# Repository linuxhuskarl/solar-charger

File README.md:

# solar-charger
## Projekt inżynierski 2019/2020

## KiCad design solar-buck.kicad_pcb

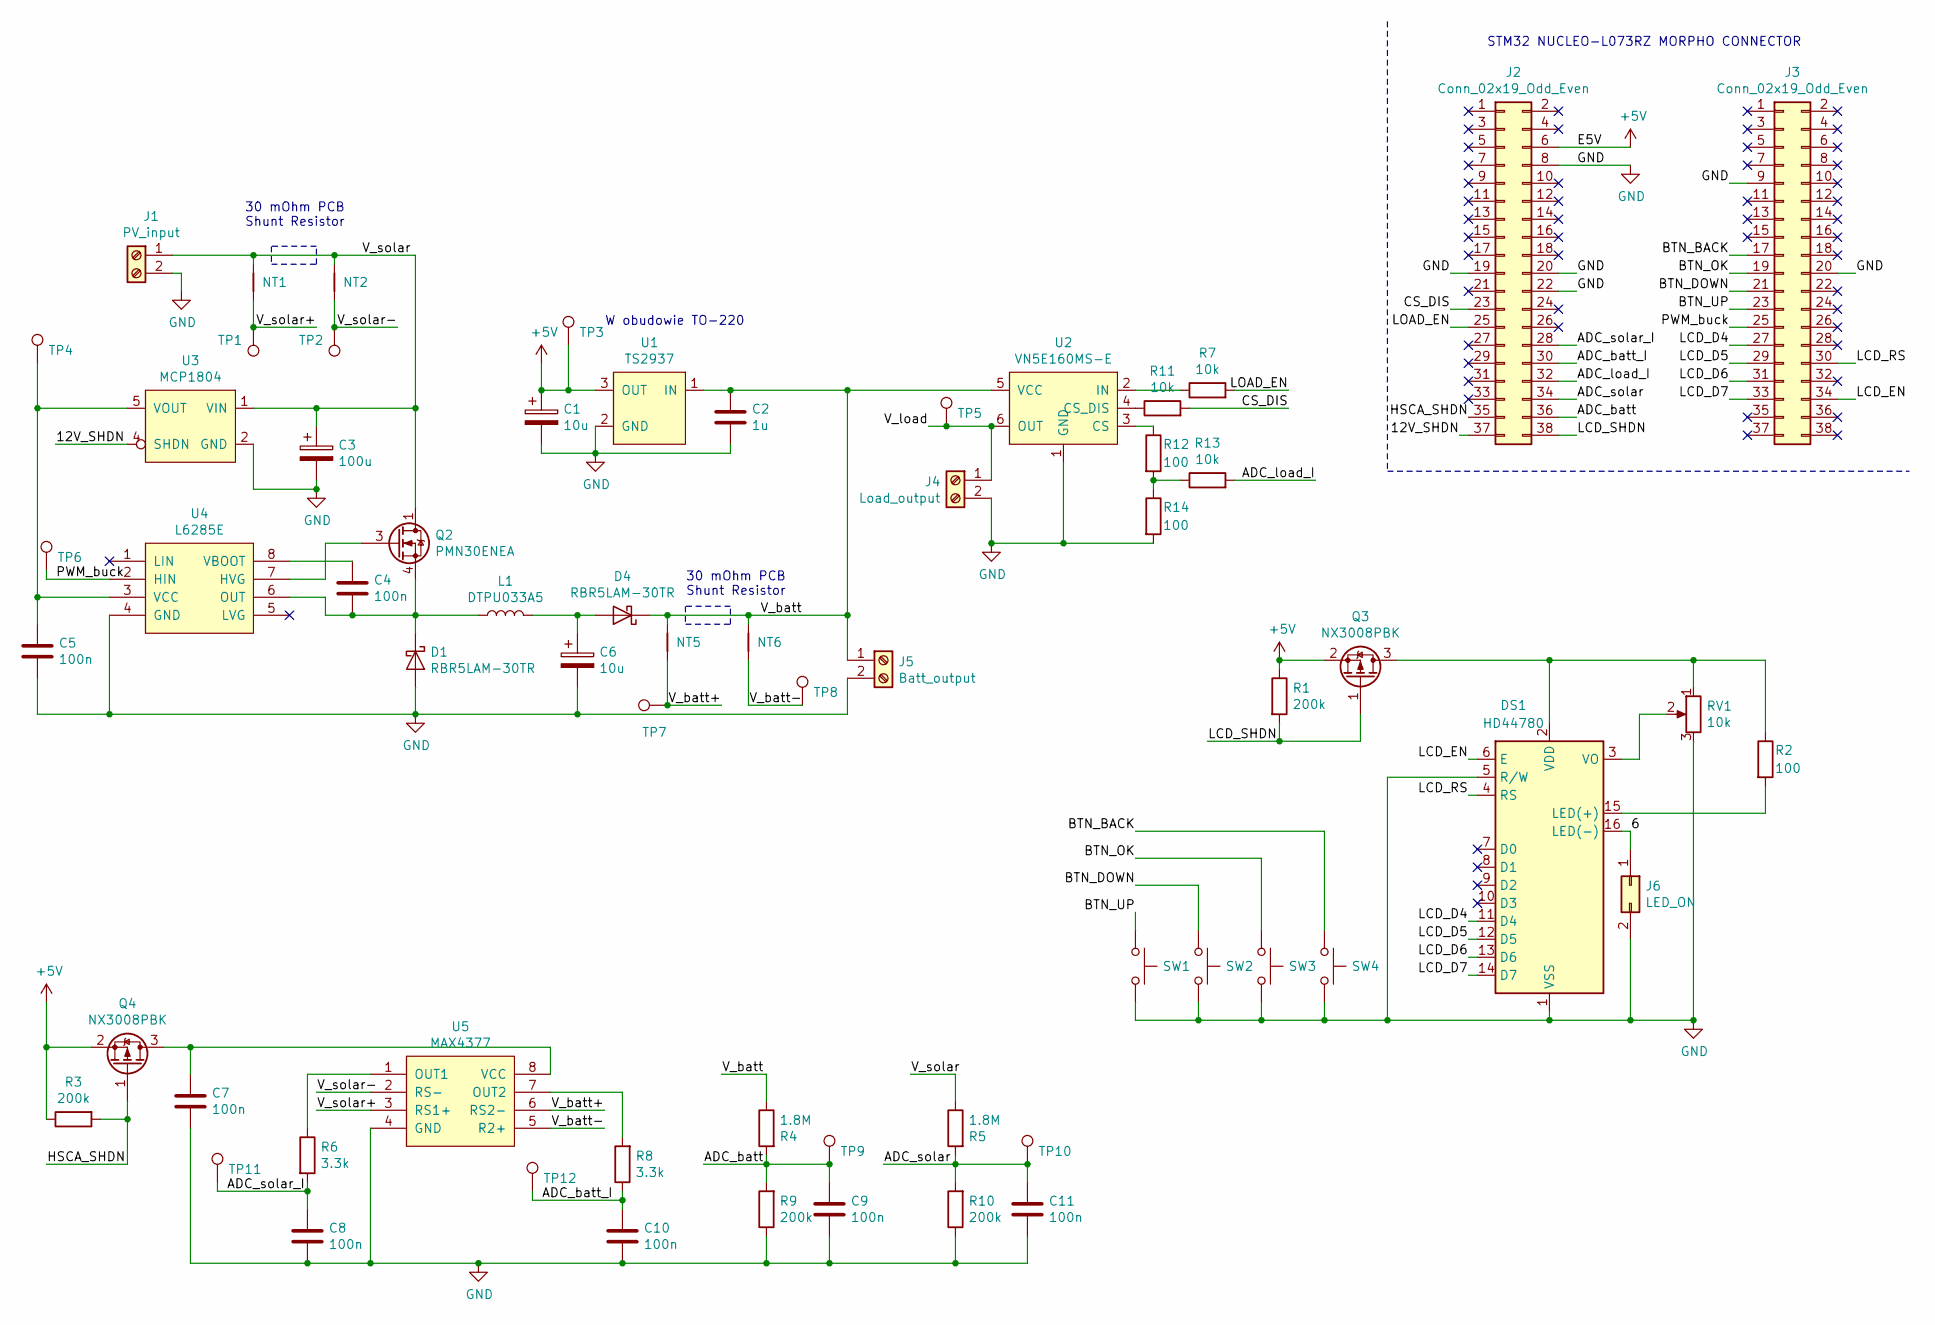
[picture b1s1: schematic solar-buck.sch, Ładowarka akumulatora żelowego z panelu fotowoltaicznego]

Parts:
C1, C6: 10u; CP_Elec_4x5.4
C2: 1u; C_0603_1608Metric_Pad1.05x0.95mm_HandSolder
C3: 100u; CP_Elec_6.3x7.7
C4, C5, C7, C8, C9, C10, C11: 100n; C_0603_1608Metric_Pad1.05x0.95mm_HandSolder
D1, D4: RBR5LAM-30TR; D_0805_2012Metric_Pad1.15x1.40mm_HandSolder
DS1: HD44780; PinSocket_1x16_P2.54mm_Vertical
J1: PV_input; TerminalBlock_bornier-2_P5.08mm
J2, J3: Conn_02x19_Odd_Even; PinSocket_2x19_P2.54mm_Vertical
J4: Load_output; TerminalBlock_bornier-2_P5.08mm
J5: Batt_output; TerminalBlock_bornier-2_P5.08mm
J6: LED_ON; PinHeader_2x01_P2.54mm_Vertical
L1: DTPU033A5
NT1, NT2, NT5, NT6: Net-Tie_2; NetTie-2_SMD_Pad8mil
Q2: PMN30ENEA; TSOP-6_1.65x3.05mm_P0.95mm
Q3, Q4: NX3008PBK; SOT-23_Handsoldering
R1, R3, R9, R10: 200k; R_0603_1608Metric_Pad1.05x0.95mm_HandSolder
R2, R12, R14: 100; R_0603_1608Metric_Pad1.05x0.95mm_HandSolder
R4, R5: 1.8M; R_0603_1608Metric_Pad1.05x0.95mm_HandSolder
R6, R8: 3.3k; R_0603_1608Metric_Pad1.05x0.95mm_HandSolder
R7, R11, R13: 10k; R_0603_1608Metric_Pad1.05x0.95mm_HandSolder
RV1: 10k; Potentiometer_Bourns_TC33X_Vertical
SW1, SW2, SW3, SW4: SW_Push; SW_PUSH_6mm
TP1, TP2, TP3, TP4, TP5, TP6, TP7, TP8, TP9, TP10, TP11, TP12: TestPoint; TestPoint_Pad_1.5x1.5mm
U1: TS2937; TO-220-3_Vertical
U2: VN5E160MS-E; SOIC-8_3.9x4.9mm_P1.27mm
U3: MCP1804; SOT-23-5_HandSoldering
U4: L6285E; SOIC-8_3.9x4.9mm_P1.27mm
U5: MAX4377; MSOP-8_3x3mm_P0.65mm

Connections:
+5V: C1.1, J2.6, Q3.2 (S), Q4.2 (S), R1.1, R3.1, TP3.1, U1.3 (OUT)
/6: DS1.16 (LED(-)), J6.1
/12V_SHDN: J2.37, U3.4 (SHDN)
/ADC_batt: C9.2, J2.36, R4.2, R9.2, TP9.1
/ADC_batt_I: C10.2, J2.30, R8.1, TP12.1
/ADC_load_I: J2.32, R13.2
/ADC_solar: C11.2, J2.34, R5.2, R10.2, TP10.1
/ADC_solar_I: C8.1, J2.28, R6.2, TP11.1
/BTN_BACK: J3.17, SW4.1
/BTN_DOWN: J3.21, SW2.1
/BTN_OK: J3.19, SW3.1
/BTN_UP: J3.23, SW1.1
/CS_DIS: J2.23, R11.2
/HSCA_SHDN: J2.35, Q4.1 (G), R3.2
/LCD_D4: DS1.11 (D4), J3.27
/LCD_D5: DS1.12 (D5), J3.29
/LCD_D6: DS1.13 (D6), J3.31
/LCD_D7: DS1.14 (D7), J3.33
/LCD_EN: DS1.6 (E), J3.34
/LCD_RS: DS1.4 (RS), J3.30
/LCD_SHDN: J2.38, Q3.1 (G), R1.2
/LOAD_EN: J2.25, R7.2
/PWM_buck: J3.25, TP6.1, U4.2 (HIN)
/V_batt: C2.1, D4.1 (K), J5.1, NT5.1, NT6.1, R4.1, U1.1 (IN), U2.5 (VCC), U2.8 (VCC)
/V_batt+: NT5.2, TP7.1, U5.6 (RS2-)
/V_batt-: NT6.2, TP8.1, U5.5 (R2+)
/V_load: J4.1, TP5.1, U2.6 (OUT), U2.7 (OUT)
/V_solar: C3.1, J1.1, NT1.1, NT2.1, Q2.1 (D), Q2.2 (D), Q2.5 (D), Q2.6 (D), R5.1, U3.1 (VIN)
/V_solar+: NT1.2, TP1.1, U5.3 (RS1+)
/V_solar-: NT2.2, TP2.1, U5.2 (RS-)
GND: C1.2, C2.2, C3.2, C5.2, C6.2, C7.2, C8.2, C9.1, C10.1, C11.1, D1.2 (A), DS1.1 (VSS), DS1.5 (R/W), J1.2, J2.8, J2.19, J2.20, J2.22, J3.9, J3.20, J4.2, J5.2, J6.2, R9.1, R10.1, R14.2, RV1.3, SW1.2, SW2.2, SW3.2, SW4.2, U1.2 (GND), U2.1 (GND), U3.2 (GND), U4.4 (GND), U5.4 (GND)
unnamed: C4.1, U4.8 (VBOOT)
unnamed: C4.2, D1.1 (K), L1.1, Q2.4 (S), U4.6 (OUT)
unnamed: C5.1, TP4.1, U3.5 (VOUT), U4.3 (VCC)
unnamed: C6.1, D4.2 (A), L1.2
unnamed: C7.1, Q4.3 (D), U5.8 (VCC)
unnamed: DS1.2 (VDD), Q3.3 (D), R2.1, RV1.1
unnamed: DS1.3 (VO), RV1.2
unnamed: DS1.15 (LED(+)), R2.2
unnamed: Q2.3 (G), U4.7 (HVG)
unnamed: R6.1, U5.1 (OUT1)
unnamed: R7.1, U2.2 (IN)
unnamed: R8.2, U5.7 (OUT2)
unnamed: R11.1, U2.4 (CS_DIS)
unnamed: R12.1, U2.3 (CS)
unnamed: R12.2, R13.1, R14.1

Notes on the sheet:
STM32 NUCLEO-L073RZ MORPHO CONNECTOR
W obudowie TO-220
30 mOhm PCB Shunt Resistor

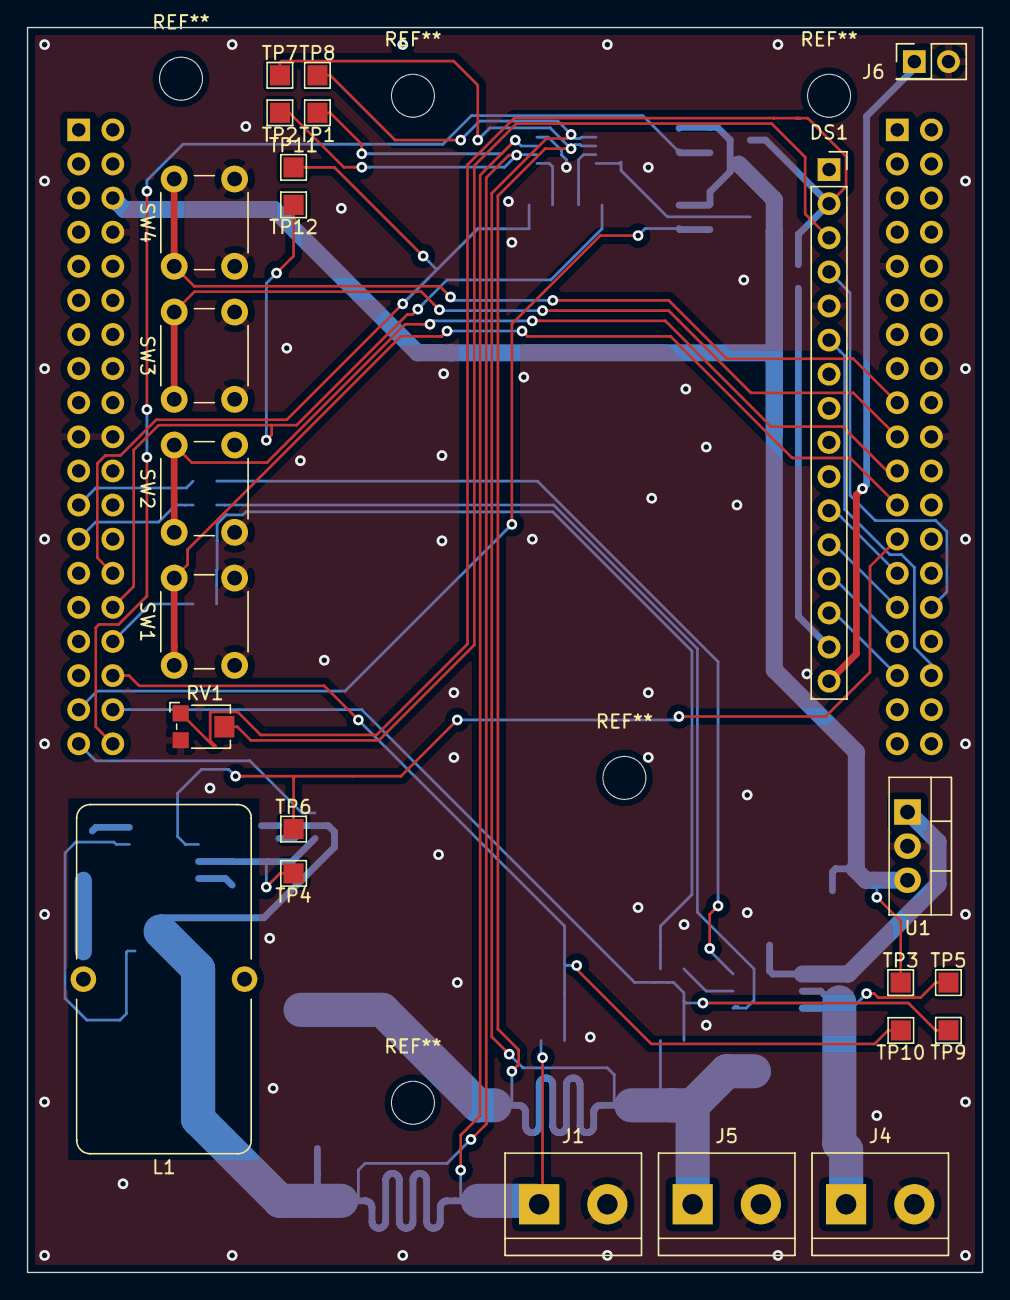
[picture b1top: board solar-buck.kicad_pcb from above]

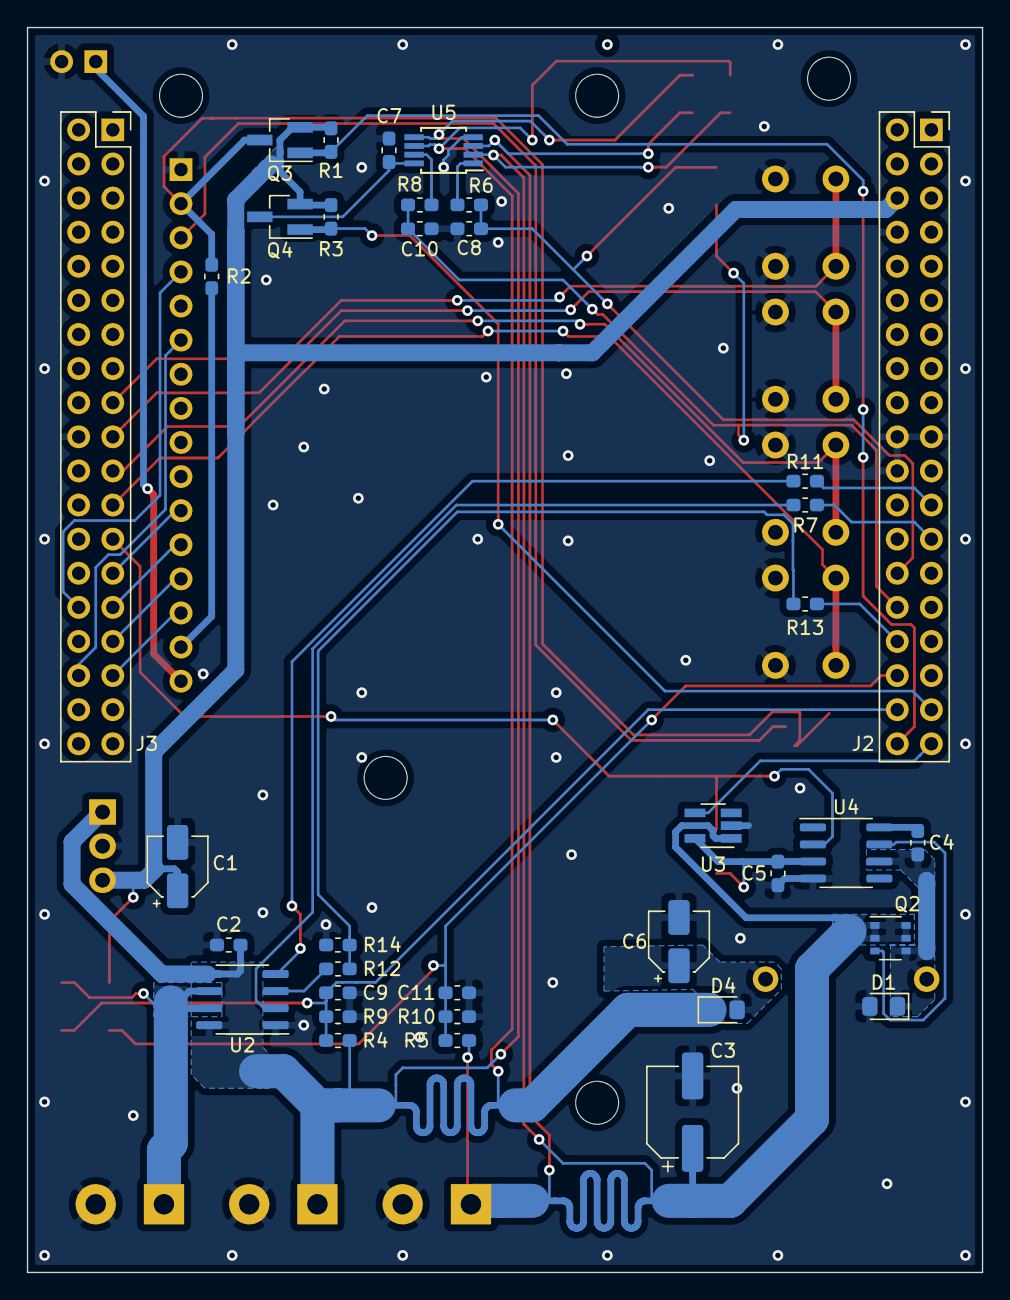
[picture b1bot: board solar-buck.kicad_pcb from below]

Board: 2 copper layers, 71.1 x 92.7 mm, 64 parts (40 on the bottom side), 46 nets.

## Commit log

2019-10-07 Removed unnessesary labels.
2019-10-08 Minor changes.
2019-10-28 Lots of changes.
2019-10-28 I exchanged some components to better ones.
2019-11-05 Updated PCB footprints
2019-11-07 PCB complete
2019-11-08 Final changes
